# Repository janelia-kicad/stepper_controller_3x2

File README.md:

- [Repository Information](#orgc9c7126)
  - [Description](#org623a5bf)
- [Images](#org1e7d118)
- [Schematic](#org1bed005)
- [Gerbers](#orga20a872)
- [Bill of Materials](#orgaaed6d6)
  - [PCB Parts](#org5e94890)
  - [Supplemental Parts](#org4c9b4c5)
  - [Vendor Parts Lists](#orge23b973)
- [Supplemental Documentation](#org541ab7a)
  - [Assembly Instructions](#org2701e28)

# Repository Information

-   **Name:** stepper\_controller\_3x2
-   **Version:** 1.2
-   **License:** Open-Source Hardware
-   **URL:** <https://github.com/janelia-kicad/stepper_controller_3x2>
-   **Author:** Peter Polidoro
-   **Email:** peter@polidoro.io

## Description

This board controls 1 stepper motor with optional forward and reverse limit switches.

# Images

# Schematic

[./schematic/stepper\_controller\_3x2.pdf](./schematic/stepper_controller_3x2.pdf)

# Gerbers

Send gerbers zip file to your favorite PCB manufacturer for fabrication.

[./gerbers/stepper\_controller\_3x2\_v1.2.zip](./gerbers/stepper_controller_3x2_v1.2.zip)

# Bill of Materials

## PCB Parts

| Item | Reference(s)           | Quantity | PartNumber        | Vendor  | Description                                                               |
|---- |---------------------- |-------- |----------------- |------- |------------------------------------------------------------------------- |
| 1    | C1 C10 C11 C4 C5 C8 C9 | 7        | 399-14636-1-ND    | digikey | CAP CER 0.1UF 50V X7R 0805                                                |
| 2    | C2 C3 C7               | 3        | 445-14419-1-ND    | digikey | CAP CER 10UF 35V X5R 0805                                                 |
| 3    | C6                     | 1        | PCE3812CT-ND      | digikey | CAP ALUM 220UF 20% 50V SMD                                                |
| 4    | CLK1                   | 1        | CTX277LVCT-ND     | digikey | OSC XO 32.000MHZ HCMOS TTL SMD                                            |
| 5    | D1                     | 1        | 568-11697-1-ND    | digikey | DIODE SCHOTTKY 45V 10A CFP15                                              |
| 6    | MDB1                   | 2        | S1011E-16-ND      | digikey | 16 Position Header Through Hole Male Pins                                 |
| 7    | P1                     | 1        | CP-063BH-ND       | digikey | CONN PWR JACK DC 2.5X5.5 8A T/H                                           |
| 8    | R1 R2                  | 2        | P10.0KCCT-ND      | digikey | RES SMD 10K OHM 1% 1/8W 0805                                              |
| 9    | R3 R4 R5 R6            | 4        | P845CCT-ND        | digikey | RES SMD 845 OHM 1% 1/8W 0805                                              |
| 10   | REG1                   | 1        | 945-1395-5-ND     | digikey | CONV DC/DC 1A 5V OUT SIP VERT                                             |
| 11   | SS1                    | 16       | ED90331-ND        | digikey | CONN PIN RCPT .025-.037 SOLDER                                            |
| 12   | T1                     | 1        | 277-1152-ND       | digikey | TERM BLOCK HDR 4POS VERT 5.08MM                                           |
| 13   | T2                     | 1        | 277-1223-ND       | digikey | TERM BLOCK HDR 4POS VERT 3.81MM                                           |
| 14   | U1                     | 1        | 1460-1071-1-ND    | digikey | IC MOTOR CONTROLLER SPI 32QFN                                             |
| 15   | U2 U4                  | 2        | 296-11603-1-ND    | digikey | IC BUF NON-INVERT 5.5V SOT23-5                                            |
| 16   | U3                     | 1        | 296-14668-1-ND    | digikey | Buffer Non-Inverting 1 Element 8 Bit per Element Push-Pull Output 20-SOIC |
| 17   | U5                     | 1        | MAX6817EUT+TCT-ND | digikey | IC DEBOUNCER SWITCH DUAL SOT23-6                                          |
| 18   | U6                     | 1        | 516-2614-1-ND     | digikey | OPTOISO 3.75KV 2CH PUSH PULL 8SO                                          |

## Supplemental Parts

| Item | Quantity | PartNumber       | Vendor  | Description                       |
|---- |-------- |---------------- |------- |--------------------------------- |
| 1    | 1        | 277-1013-ND      | digikey | TERM BLOCK PLUG 4POS STR 5.08MM   |
| 2    | 1        | 277-1042-ND      | digikey | TERM BLOCK PLUG 4POS 5.08MM       |
| 3    | 1        | 277-1163-ND      | digikey | TERM BLOCK PLUG 4POS STR 3.81MM   |
| 4    | 1        | 277-1193-ND      | digikey | TERM BLOCK PLUG 4POS 90DEG 3.81MM |
| 5    | 1        | 1460-1187-ND     | digikey | TMC2130 STEPPER DRIVER BOARD      |
| 6    | 1        | 501100B00000G-ND | digikey | HEATSINK 14-DIP/16-DIP            |
| 7    | 1        | 3M10315-ND       | digikey | TAPE ADHESIVE TRANSFER 1/2in X5YD |

## Vendor Parts Lists

[./bom/digikey\_parts.csv](./bom/digikey_parts.csv)

[./bom/supplemental\_digikey\_parts.csv](./bom/supplemental_digikey_parts.csv)

# Supplemental Documentation

## Assembly Instructions

-   Solder header pins into the stepper driver board, making note of TOP label. Insert header pins on bottom of board so that the long unsoldered header pins point down when the TOP label faces up.
-   Expose one side of the thermal adhesive tape and attach to the bottom of the heatsink. Trim tape so it does not extend beyond heatsink edges.
-   Expose the other side of the thermal adhesive tape and attach the heatsink to the stepper driver board on the side with the TOP label.
-   Solder surface mount and through hole components onto the pcb.
-   Insert stepper driver board into pin receptacles.

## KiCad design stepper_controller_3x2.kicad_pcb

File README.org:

# Created 2019-04-12 Fri 13:52
#+OPTIONS: title:nil author:nil email:nil toc:t |:t ^:nil
* Repository Information

- Name :: stepper_controller_3x2
- Version :: 1.2
- License :: Open-Source Hardware
- URL :: https://github.com/janelia-kicad/stepper_controller_3x2
- Author :: Peter Polidoro
- Email :: peter@polidoro.io

** Description

This board controls 1 stepper motor with optional forward and reverse
limit switches.

* Images

* Schematic

[[file:./schematic/stepper_controller_3x2.pdf][./schematic/stepper_controller_3x2.pdf]]

[[file:./schematic/images/schematic00.png]]

[[file:./schematic/images/schematic01.png]]

[[file:./schematic/images/schematic02.png]]

* Gerbers

Send gerbers zip file to your favorite PCB manufacturer for fabrication.

[[file:./gerbers/stepper_controller_3x2_v1.2.zip][./gerbers/stepper_controller_3x2_v1.2.zip]]

[[file:./gerbers/images/gerbers00.png]]

[[file:./gerbers/images/gerbers01.png]]

* Bill of Materials

** PCB Parts

| Item | Reference(s)           | Quantity | PartNumber        | Vendor  | Description                                                               |
|------+------------------------+----------+-------------------+---------+---------------------------------------------------------------------------|
|    1 | C1 C10 C11 C4 C5 C8 C9 |        7 | 399-14636-1-ND    | digikey | CAP CER 0.1UF 50V X7R 0805                                                |
|    2 | C2 C3 C7               |        3 | 445-14419-1-ND    | digikey | CAP CER 10UF 35V X5R 0805                                                 |
|    3 | C6                     |        1 | PCE3812CT-ND      | digikey | CAP ALUM 220UF 20% 50V SMD                                                |
|    4 | CLK1                   |        1 | CTX277LVCT-ND     | digikey | OSC XO 32.000MHZ HCMOS TTL SMD                                            |
|    5 | D1                     |        1 | 568-11697-1-ND    | digikey | DIODE SCHOTTKY 45V 10A CFP15                                              |
|    6 | MDB1                   |        2 | S1011E-16-ND      | digikey | 16 Position Header Through Hole Male Pins                                 |
|    7 | P1                     |        1 | CP-063BH-ND       | digikey | CONN PWR JACK DC 2.5X5.5 8A T/H                                           |
|    8 | R1 R2                  |        2 | P10.0KCCT-ND      | digikey | RES SMD 10K OHM 1% 1/8W 0805                                              |
|    9 | R3 R4 R5 R6            |        4 | P845CCT-ND        | digikey | RES SMD 845 OHM 1% 1/8W 0805                                              |
|   10 | REG1                   |        1 | 945-1395-5-ND     | digikey | CONV DC/DC 1A 5V OUT SIP VERT                                             |
|   11 | SS1                    |       16 | ED90331-ND        | digikey | CONN PIN RCPT .025-.037 SOLDER                                            |
|   12 | T1                     |        1 | 277-1152-ND       | digikey | TERM BLOCK HDR 4POS VERT 5.08MM                                           |
|   13 | T2                     |        1 | 277-1223-ND       | digikey | TERM BLOCK HDR 4POS VERT 3.81MM                                           |
|   14 | U1                     |        1 | 1460-1071-1-ND    | digikey | IC MOTOR CONTROLLER SPI 32QFN                                             |
|   15 | U2 U4                  |        2 | 296-11603-1-ND    | digikey | IC BUF NON-INVERT 5.5V SOT23-5                                            |
|   16 | U3                     |        1 | 296-14668-1-ND    | digikey | Buffer Non-Inverting 1 Element 8 Bit per Element Push-Pull Output 20-SOIC |
|   17 | U5                     |        1 | MAX6817EUT+TCT-ND | digikey | IC DEBOUNCER SWITCH DUAL SOT23-6                                          |
|   18 | U6                     |        1 | 516-2614-1-ND     | digikey | OPTOISO 3.75KV 2CH PUSH PULL 8SO                                          |

** Supplemental Parts

| Item | Quantity | PartNumber       | Vendor  | Description                       |
|------+----------+------------------+---------+-----------------------------------|
|    1 |        1 | 277-1013-ND      | digikey | TERM BLOCK PLUG 4POS STR 5.08MM   |
|    2 |        1 | 277-1042-ND      | digikey | TERM BLOCK PLUG 4POS 5.08MM       |
|    3 |        1 | 277-1163-ND      | digikey | TERM BLOCK PLUG 4POS STR 3.81MM   |
|    4 |        1 | 277-1193-ND      | digikey | TERM BLOCK PLUG 4POS 90DEG 3.81MM |
|    5 |        1 | 1460-1187-ND     | digikey | TMC2130 STEPPER DRIVER BOARD      |
|    6 |        1 | 501100B00000G-ND | digikey | HEATSINK 14-DIP/16-DIP            |
|    7 |        1 | 3M10315-ND       | digikey | TAPE ADHESIVE TRANSFER 1/2in X5YD |

** Vendor Parts Lists

[[file:./bom/digikey_parts.csv][./bom/digikey_parts.csv]]

[[file:./bom/supplemental_digikey_parts.csv][./bom/supplemental_digikey_parts.csv]]

* Supplemental Documentation

** Assembly Instructions

- Solder header pins into the stepper driver board, making note of TOP label.
  Insert header pins on bottom of board so that the long unsoldered header
  pins point down when the TOP label faces up.
- Expose one side of the thermal adhesive tape and attach to the bottom of the
  heatsink. Trim tape so it does not extend beyond heatsink edges.
- Expose the other side of the thermal adhesive tape and attach the heatsink
  to the stepper driver board on the side with the TOP label.
- Solder surface mount and through hole components onto the pcb.
- Insert stepper driver board into pin receptacles.

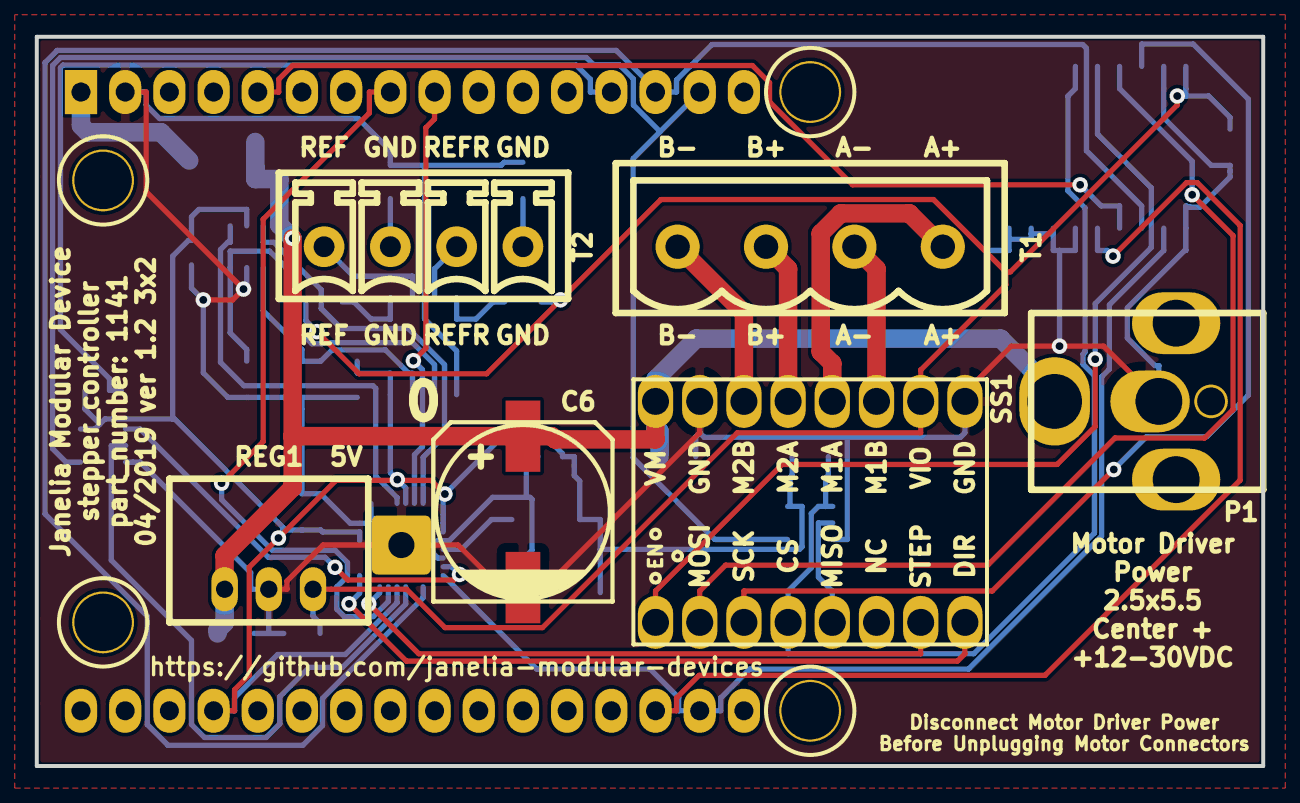
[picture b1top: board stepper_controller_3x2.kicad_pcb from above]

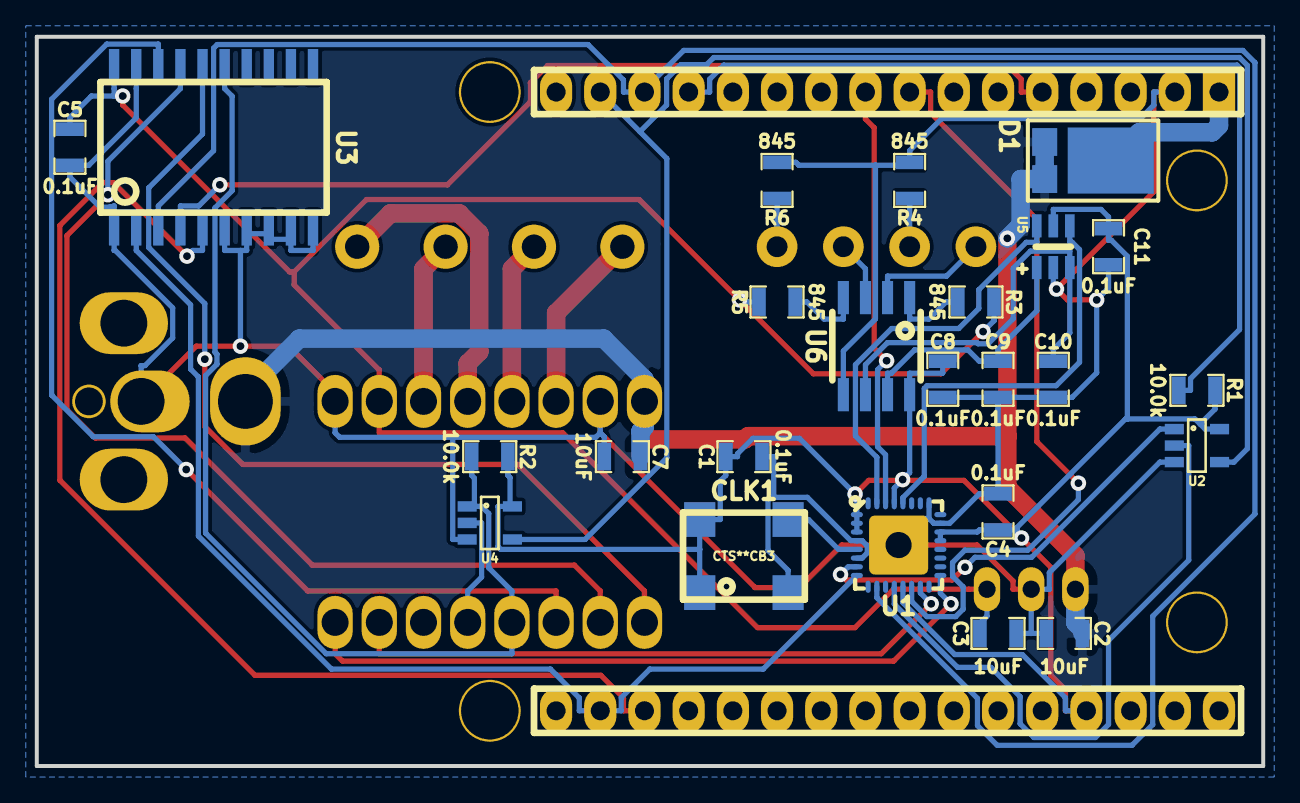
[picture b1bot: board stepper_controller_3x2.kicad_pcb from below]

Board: 2 copper layers, 70.5 x 41.9 mm, 31 parts (24 on the bottom side), 37 nets.

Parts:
C1, C4, C5, C8, C9, C10, C11: 0.1uF; SM0805
C2, C3, C7: 10uF; SM0805
C6: 220uF_POL; C_ELEC_10
CLK1: CLK_32MHZ; CTS_SMD_4_7X5MM
D1: diode_schottky_45V_10A; CFP15
MDB1: VAL**; MODULAR_DEVICE_BASE_3X2_MALE
P1: PWR_JACK_2.5x5.5; DCJACK_2PIN_HIGHCURRENT
R1, R2: 10.0k; SM0805
R3, R4, R5, R6: 845; SM0805
REG1: CONV_DC_DC_5V_1A; DC_DC_CONV_R78C
SS1: STEPSTICK
T1: TERM_BLK_HDR_4POS_VERT_0.2IN
T2: TERM_BLK_HDR_4POS_VERT_0.150IN
U1: TMC429; QFN-5x5-32
U2, U4: BUFFER_TRI_STATE; SOT-23-5
U3: SN74ABT541BDWR; SOIC_20
U5: VAL**; MAX6817
U6: OPTOISO_2CHAN; SO-8

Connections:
+3V3: C1.1, C4.1, C8.1, C11.1, CLK1.1, CLK1.4, MDB1.3V3, R1.1, R2.1, U1.1, U1.2, U1.3, U1.13, U1.21, U1.22, U1.29, U2.5, U4.5, U5.5, U6.8
+5V: C3.1, C5.1, R3.1, R5.1, REG1.3, SS1.15, U3.20
/CLK: CLK1.3, U1.5
/CS_429: MDB1.10, R1.2
/CS_DRIVER_0: MDB1.14, U3.5
/ENABLE_0: MDB1.2, U3.4
/INT: MDB1.5, U1.14
/MISO: MDB1.12, U2.4, U4.4
/MOSI: MDB1.11, U1.10, U3.3
/POSCOMP: MDB1.6, U1.30
/SCK: MDB1.13, U1.8, U3.2
/tmc429_driver_0/DIR_0: SS1.1, U1.17
/tmc429_driver_0/MISO_UB: U1.12, U2.2
/tmc429_driver_0/MOSI_B: SS1.7, U3.17
/tmc429_driver_0/REFR_0: U1.28, U5.4
/tmc429_driver_0/REF_0: U1.31, U5.6
/tmc429_driver_0/SCK_B: SS1.6, U3.18
/tmc429_driver_0/STEP_0: SS1.2, U1.15
/tmc429_driver_0/stepper_0/A_+: SS1.13, T1.4
/tmc429_driver_0/stepper_0/A_-: SS1.14, T1.3
/tmc429_driver_0/stepper_0/B_+: SS1.12, T1.2
/tmc429_driver_0/stepper_0/B_-: SS1.11, T1.1
/tmc429_driver_0/stepper_0/MISO_UB: SS1.4, U4.2
/tmc429_driver_0/stepper_0/REFR_B: T2.3, U6.3
/tmc429_driver_0/stepper_0/REFR_BI: C10.1, U5.3, U6.6
/tmc429_driver_0/stepper_0/REFR_GND: R6.1, T2.4
/tmc429_driver_0/stepper_0/REFR_PWR: R5.2, U6.4
/tmc429_driver_0/stepper_0/REF_B: T2.1, U6.2
/tmc429_driver_0/stepper_0/REF_BI: C9.1, U5.1, U6.7
/tmc429_driver_0/stepper_0/REF_GND: R4.1, T2.2
/tmc429_driver_0/stepper_0/REF_PWR: R3.2, U6.1
/tmc429_driver_0/~CS: U1.7, U2.1
/tmc429_driver_0/~CS_DRIVER_0_B: R2.2, SS1.5, U3.15, U4.1
/tmc429_driver_0/~ENABLE_0_B: SS1.8, U3.16
GND: C1.2, C2.2, C3.2, C4.2, C5.2, C6.2, C7.2, C8.2, C9.2, C10.2, C11.2, CLK1.2, MDB1.GND, P1.2, R4.2, R6.2, REG1.2, SS1.10, SS1.16, U1.4, U1.6, U1.23, U1.25, U1.PAD, U2.3, U3.1, U3.6, U3.7, U3.8, U3.9, U3.10, U3.19, U4.3, U5.2, U6.5
VAA: C2.1, C6.1, C7.1, D1.2, P1.1, REG1.1, SS1.9
VDD: D1.1, MDB1.VDD

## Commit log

2017-03-29 Initial commit.
2017-03-29 Renamed files.
2017-03-29 Removed footprint.
2017-03-30 Renamed tmc260 -> tmc26x.
2017-03-30 Added TERM_BLK_HDR_4POS_VERT_0.150IN.kicad_mod.
2017-03-30 Updated bom.
2017-03-30 Modifications.
2017-03-30 Added TMC260.
2017-03-31 Moved pin.
2017-03-31 First attempt at layout.
2017-03-31 Removed extra files.
2017-06-15 tmc26x -> driver.
2017-06-15 Mostly finished with v1.0.
2017-06-15 Switched component.
2017-06-15 Removed .cmp file.
2017-06-19 Finished v1.0.
2017-09-13 Updated 0.1uF capacitors.
2017-09-22 Removed extra libraries.
2017-10-23 Moved footprints.
2017-10-24 More progress towards v1.1.
2017-10-25 Finished version 1.1.
2018-01-08 Updated to v4.
2018-01-08 Added v4 files.
2018-01-08 Updated gitignore.
2018-03-09 Update license from software to hardware.
2018-04-12 README.md -> README.org.
2018-04-19 Added .DS_Store to .gitignore.
2018-05-16 Added generate_kicad_documentation submodule.
2018-05-17 Updated submodules.
2018-08-12 Marked extra Teensy pins.
2018-08-12 Removed v4 files.
2018-08-24 Removed F.SilkS from pads.
2018-08-27 Removed *.SilkS from pads.
2019-03-28 Progess towards v1.2
2019-04-02 Progress towards v1.2
2019-04-12 Add limit switch filter capacitors
2021-09-16 Update email address
2021-09-21 Remove ignored files
2022-02-22 Add guix files
2022-02-23 Add guix documentation
